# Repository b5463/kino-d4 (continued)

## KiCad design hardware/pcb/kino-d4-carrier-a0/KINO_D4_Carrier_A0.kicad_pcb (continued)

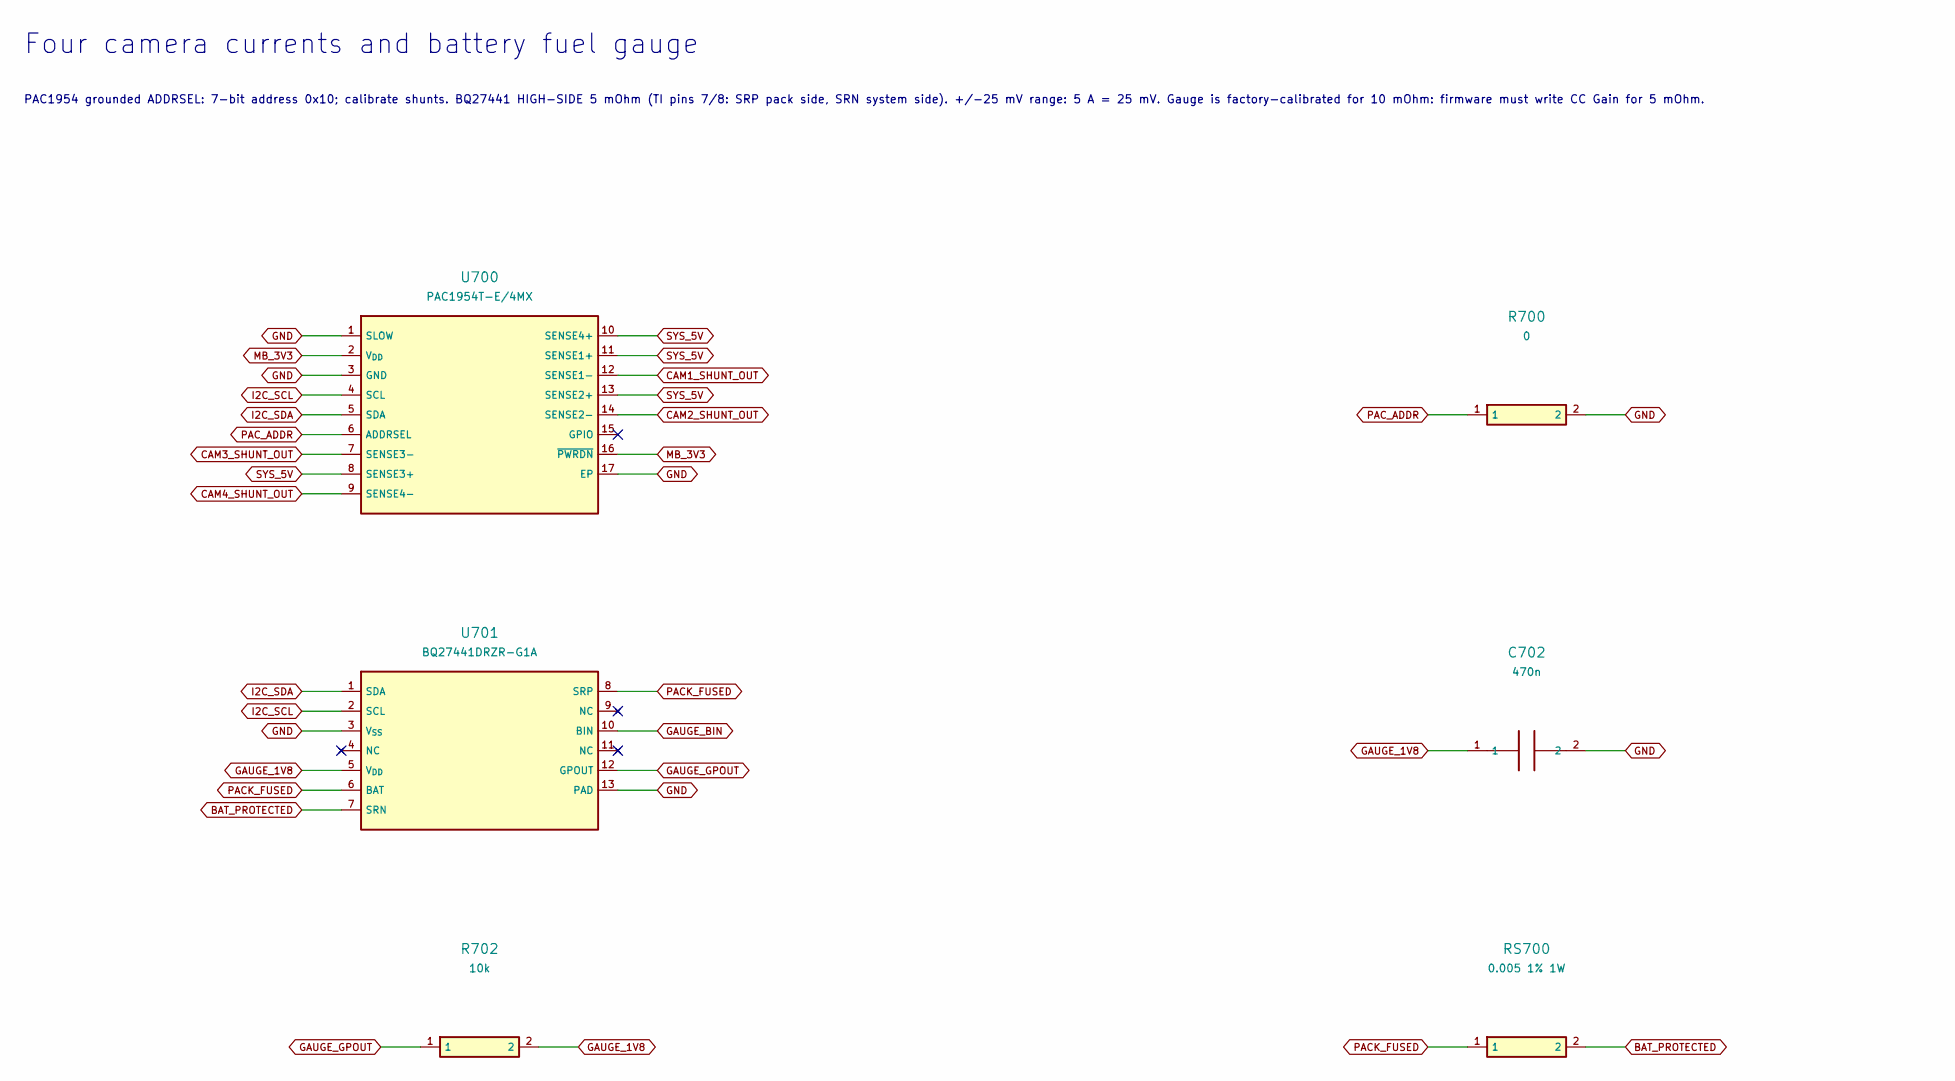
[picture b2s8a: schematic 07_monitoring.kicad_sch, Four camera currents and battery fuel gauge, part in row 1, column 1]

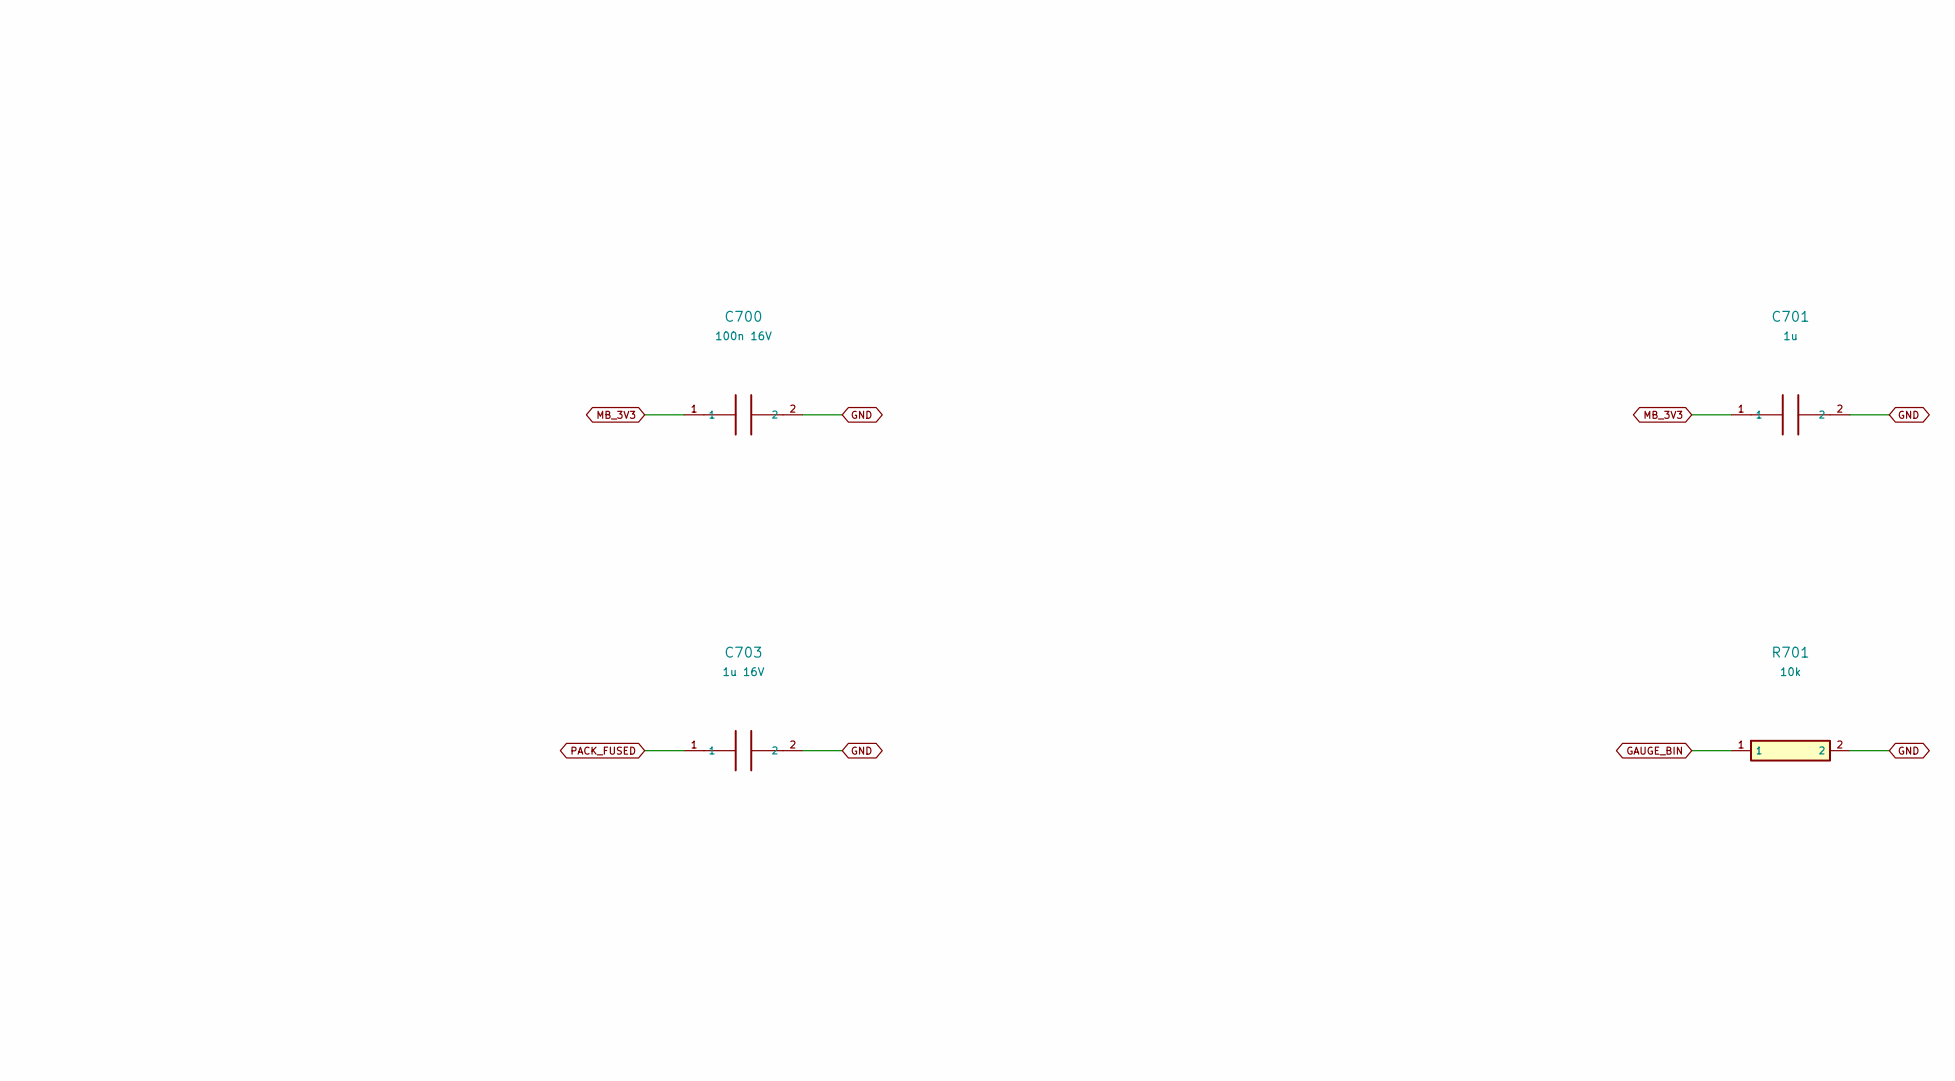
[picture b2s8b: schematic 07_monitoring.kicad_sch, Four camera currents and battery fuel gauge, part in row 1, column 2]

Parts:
C700: 100n 16V; C_0603_1608Metric
C701: 1u; C_0603_1608Metric
C702: 470n; C_0603_1608Metric
C703: 1u 16V; C_0603_1608Metric
R700: 0; R_0603_1608Metric
R701, R702: 10k; R_0603_1608Metric
RS700: 0.005 1% 1W; R_1206_3216Metric
U700: PAC1954T-E/4MX; VQFN-16-1EP_3x3mm_P0.5mm_EP1.1x1.1mm
U701: BQ27441DRZR-G1A; Texas_S-PDSO-N12

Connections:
CAM1_SHUNT_OUT: U700.12 (SENSE1-); also elsewhere on the board
CAM2_SHUNT_OUT: U700.14 (SENSE2-); also elsewhere on the board
CAM3_SHUNT_OUT: U700.7 (SENSE3-); also elsewhere on the board
CAM4_SHUNT_OUT: U700.9 (SENSE4-); also elsewhere on the board
GAUGE_1V8: C702.1, R702.2, U701.5 (V_{DD})
GAUGE_BIN: R701.1, U701.10 (BIN)
I2C_SCL: U700.4 (SCL), U701.2 (SCL); also elsewhere on the board
I2C_SDA: U700.5 (SDA), U701.1 (SDA); also elsewhere on the board
MB_3V3: C700.1, C701.1, U700.2 (V_{DD}), U700.16 (~PWRDN); also elsewhere on the board
unnamed: R702.1, U701.12 (GPOUT)
PAC_ADDR: R700.1, U700.6 (ADDRSEL)
SYS_5V: U700.8 (SENSE3+), U700.10 (SENSE4+), U700.11 (SENSE1+), U700.13 (SENSE2+); also elsewhere on the board

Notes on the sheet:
Four camera currents and battery fuel gauge
PAC1954 grounded ADDRSEL: 7-bit address 0x10; calibrate shunts. BQ27441 HIGH-SIDE 5 mOhm (TI pins 7/8: SRP pack side, SRN system side). +/-25 mV range: 5 A = 25 mV. Gauge is factory-calibrated for 10 mOhm: firmware must write CC Gain for 5 mOhm.

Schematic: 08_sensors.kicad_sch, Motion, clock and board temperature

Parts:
C800, C801, C802, C803: 100n 16V; C_0603_1608Metric
J800: 3V PRIMARY RTC BACKUP; JST_GH_BM02B-GHS-TBT_1x02-1MP_P1.25mm_Vertical
R800: 10k; R_0603_1608Metric
U800: LSM6DSOXTR; LGA-14_3x2.5mm_P0.5mm_LayoutBorder3x4y
U801: RV-3028-C7; MicroCrystal_C7_SON-8_1.5x3.2mm_P0.9mm
U802: TMP117AIDRVR; WSON-6-1EP_2x2mm_P0.65mm_EP1x1.6mm

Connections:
I2C_SCL: U800.13 (SCL), U801.3 (SCL), U802.1 (SCL); also elsewhere on the board
I2C_SDA: U800.14 (SDA), U801.4 (SDA), U802.6 (SDA); also elsewhere on the board
IMU_INT: U800.4 (INT1); also elsewhere on the board
MB_3V3: C800.1, C801.1, C802.1, C803.1, R800.2, U800.5 (VDDIO), U800.8 (VDD), U800.12 (CS), U801.7 (VDD), U802.5 (V+); also elsewhere on the board
RTC_BACKUP: J800.1 (RTC_BACKUP), U801.6 (VBACKUP)
RTC_INT_N: R800.1, U801.2 (~INT); also elsewhere on the board

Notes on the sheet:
Motion, clock and board temperature
IMU mode 1; axes marked on PCB. RTC backup charging must stay disabled for primary cell. No always-on wake promise.

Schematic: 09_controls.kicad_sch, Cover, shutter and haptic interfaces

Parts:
C900, C901: 1u; C_0603_1608Metric
C902: 10u; C_0805_2012Metric
C903: 10n; C_0603_1608Metric
C904: 100n; C_0603_1608Metric
C905: 100n 16V; C_0603_1608Metric
D900, D901, D902: PESD5V0S1BA; D_SOD-323
J900: HAPTIC MOTOR; JST_GH_BM02B-GHS-TBT_1x02-1MP_P1.25mm_Vertical
J901: COVER HALL SENSOR; JST_GH_BM03B-GHS-TBT_1x03-1MP_P1.25mm_Vertical
J902: LOCAL SHUTTER; JST_GH_BM02B-GHS-TBT_1x02-1MP_P1.25mm_Vertical
J903: REMOTE DRY CONTACT; JST_GH_BM02B-GHS-TBT_1x02-1MP_P1.25mm_Vertical
J904: FUNCTION BUTTON; JST_GH_BM02B-GHS-TBT_1x02-1MP_P1.25mm_Vertical
Q900: 2N7002; SOT-23
R900, R905: 100k; R_0603_1608Metric
R901: 1k; R_0603_1608Metric
R902, R903, R906: 10k; R_0603_1608Metric
R904: 47k; R_0603_1608Metric
U900: DRV2605LDGSR; TSSOP-10_3x3mm_P0.5mm
U901: SN74LVC1G14DBVR; SOT-23-5

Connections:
COVER_N: C903.1, R901.2, R902.1; also elsewhere on the board
COVER_RAW: D901.2 (A), J901.3 (COVER_RAW), R901.1
FN_N: J904.1 (FN_N), R906.1; also elsewhere on the board
HAPTIC_EN: R900.1, U900.5 (EN); also elsewhere on the board
HAPTIC_REG: C900.1, U900.1 (REG)
I2C_SCL: U900.2 (SCL); also elsewhere on the board
I2C_SDA: U900.3 (SDA); also elsewhere on the board
MB_3V3: C901.1, C902.1, C905.1, J901.1 (MB_3V3), R902.2, R904.2, R906.2, U900.6 (VDD/NC), U900.10 (VDD), U901.5 (VCC); also elsewhere on the board
MOTOR_N: J900.2 (MOTOR_N), U900.9 (OUT-)
MOTOR_P: J900.1 (MOTOR_P), U900.7 (OUT+)
REMOTE_ACTIVE: Q900.1 (G), R905.1, U901.4 (Y)
REMOTE_CONTACT: D900.2 (A), J903.1 (REMOTE_CONTACT), R903.1
REMOTE_FILTER: C904.1, R903.2, R904.1, U901.2 (A)
SHUTTER_N: D902.2 (A), J902.1 (SHUTTER_N), Q900.3 (D); also elsewhere on the board

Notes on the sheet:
Cover, shutter and haptic interfaces
Passive dry-contact remote only. Haptic firmware must suppress vibration through exposure and settling. Motor MPN remains to be selected.

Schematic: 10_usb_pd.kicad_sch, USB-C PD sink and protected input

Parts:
C1000: 1u 35V; C_0805_2012Metric
C1001, C1002: 1u; C_0603_1608Metric
D1000: BZT52C10; D_SOD-123
D1001: SMF12A; D_SOD-123F
D1002, D1003: PESD24VL1BA; D_SOD-323
J1000: USB4105-GF-A; USB_C_GCT_USB4105_KINO_GND0.05
Q1000, Q1001: AO4407A; SOIC-8_3.9x4.9mm_P1.27mm
R1000, R1003: 100k; R_0603_1608Metric
R1001: 470; R_0603_1608Metric
R1002, R1004: 1k; R_0603_1608Metric
TP1000: USB_VBUS; TestPoint_Pad_D1.5mm
TP1001: PD_9V_OK_N; TestPoint_Pad_D1.5mm
U1000: STUSB4500QTR; QFN-24-1EP_4x4mm_P0.5mm_EP2.7x2.7mm

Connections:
I2C_SCL: U1000.7 (SCL); also elsewhere on the board
I2C_SDA: U1000.8 (SDA); also elsewhere on the board
PD_1V2: C1001.1, U1000.21 (VREG_1V2)
PD_2V7: C1002.1, U1000.23 (VREG_2V7)
PD_9V_OK_N: TP1001.1, U1000.20 (POWER_OK2)
PD_COMMON_SOURCE: D1000.1 (K), Q1000.1 (S), Q1000.2 (S), Q1000.3 (S), Q1001.1 (S), Q1001.2 (S), Q1001.3 (S), R1003.1
PD_DISCH: R1002.2, U1000.9 (DISCH)
PD_GATE: D1000.2 (A), Q1000.4 (G), Q1001.4 (G), R1003.2, R1004.1
PD_RESET: R1000.1, U1000.6 (RESET)
PD_SINK_EN_N: R1004.2, U1000.16 (VBUS_EN_SNK)
PD_VBUS_SENSE: R1001.2, U1000.18 (VBUS_VS_DISCH)
USB_CC1: D1002.1 (K), J1000.A5 (CC1), U1000.1 (CC1DB), U1000.2 (CC1)
USB_CC2: D1003.1 (K), J1000.B5 (CC2), U1000.4 (CC2), U1000.5 (CC2DB)
USB_VBUS: C1000.1, D1001.1 (K), J1000.A4 (VBUS), J1000.A9 (VBUS), J1000.B4 (VBUS), J1000.B9 (VBUS), Q1000.5 (D), Q1000.6 (D), Q1000.7 (D), Q1000.8 (D), R1001.1, TP1000.1, U1000.24 (VDD)

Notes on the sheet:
USB-C PD sink and protected input
Charge-only port. STUSB4500 NVM must be programmed for 5V fallback and 9V/2A. Protection and gate transient review OPEN.

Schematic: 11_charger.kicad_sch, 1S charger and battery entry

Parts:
C1100: 1n 50V; C_0603_1608Metric
C1101: 4.7u 10V; C_0805_2012Metric
C1102, C1103: 47n 16V; C_0603_1608Metric
C1104, C1105, C1107, C1108, C1109, C1111, C1112, C1113, C1114, C1115, C1117, C1118: 10u 35V X7R; C_1206_3216Metric
C1106, C1110, C1116, C1119: 100n 35V; C_0603_1608Metric
F1100: 7A fast 1206; Fuse_1206_3216Metric
J1100: PROTECTED 1S PACK / NTC; JST_VH_B3P-VH_1x03_P3.96mm_Vertical
L1100: 1.0uH 14.1A Isat; L_TDK_SPM6530
R1100: 3.00k 1%; R_0603_1608Metric
R1101: 100; R_0603_1608Metric
R1102: 100k; R_0603_1608Metric
R1104, R1107: 30.1k 1%; R_0603_1608Metric
R1105: 10k 1%; R_0603_1608Metric
R1106: 5.23k 1%; R_0603_1608Metric
R1108: 0; R_0603_1608Metric
R1109: 10k; R_0603_1608Metric
R1110: 10k; R_0603_1608Metric; not fitted
TP1100: CHARGE_STAT_N; TestPoint_Pad_D1.5mm
TP1101: SYS_RAW; TestPoint_Pad_D1.5mm
U1100: BQ25798RQMR; Texas_RQM0029A_VQFN-29_4x4mm_P0.4mm

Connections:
CHARGE_CE_N: R1102.1, R1110.1, U1100.13 (~CE); also elsewhere on the board
CHARGE_STAT_N: R1109.1, TP1100.1, U1100.1 (STAT); also elsewhere on the board
CHG_BATP: R1101.2, U1100.18 (BATP)
CHG_BTST1: C1102.1, U1100.4 (BTST1)
CHG_BTST2: C1103.1, U1100.19 (BTST2)
CHG_ILIM: R1104.2, R1105.1, U1100.17 (ILIM_HIZ)
CHG_PMID: C1107.1, C1108.1, C1109.1, C1110.1, U1100.29 (PMID)
CHG_PROG: R1100.1, U1100.20 (PROG)
CHG_SDRV: C1100.1, U1100.24 (SDRV)
CHG_SW1: C1102.2, L1100.1, U1100.28 (SW1)
CHG_SW2: C1103.2, L1100.2, U1100.26 (SW2)
CHG_TS: R1106.2, R1107.1, R1108.1, U1100.16 (TS)
I2C_SCL: U1100.14 (SCL); also elsewhere on the board
I2C_SDA: U1100.15 (SDA); also elsewhere on the board
MB_3V3: R1109.2; also elsewhere on the board
PACK_NTC: J1100.2 (PACK_NTC), R1108.2
PACK_PLUS: F1100.1, J1100.1 (PACK_PLUS)
SYS_RAW: C1111.1, C1112.1, C1113.1, C1114.1, C1115.1, C1116.1, TP1101.1, U1100.25 (SYS); also elsewhere on the board

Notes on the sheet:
1S charger and battery entry
CE pulled LOW: charges with the camera off, POR defaults 4.2 V / 1 A (PROG 3.00k, TI tables 7-1/7-2). 103AT-2 pack NTC, TS window 1-60 C (TI RT1 5.24k / RT2 30.31k). Open or shorted NTC suspends charge. Fit R1110 only to inhibit charging at bring-up.

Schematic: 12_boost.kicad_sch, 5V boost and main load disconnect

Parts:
C1200: 3.3n 50V; C_0603_1608Metric
C1201: 100p; C_0603_1608Metric; not fitted
C1202: 4.7u 16V; C_0603_1608Metric
C1203: 100n; C_0603_1608Metric
C1204, C1206, C1207, C1208, C1209, C1210, C1211: 22u 10V; C_1206_3216Metric
C1205: 100n 16V; C_0603_1608Metric
C1212: 10u; C_0805_2012Metric
C1213: 22u; C_0805_2012Metric
D1200: SS34; D_SMA
JP1200: REMOVE FOR P4 USB SERVICE; PinHeader_1x02_P2.54mm_Vertical
L1200: 2.2uH 19.6A Isat; L_Coilcraft_XAL7070-XXX
L1201: 2.2uH 1.5A; L_Taiyo-Yuden_NR-30xx
Q1200, Q1201: AO4407A; SOIC-8_3.9x4.9mm_P1.27mm
Q1202: 2N7002; SOT-23
R1200: 110k 0.1%; R_0603_1608Metric
R1201: 15k 0.1%; R_0603_1608Metric
R1202: 20.5k 1%; R_0603_1608Metric
R1203: 100k; R_0603_1608Metric
TP1200: SYS_5V; TestPoint_Pad_D1.5mm
TP1201: MB_3V3; TestPoint_Pad_D1.5mm
TP1202: GND; TestPoint_Pad_D1.5mm
U1200: TPS61288LRQQR; TPS61288_RQQ0011A_DRAFT
U1201: TPS62162DSGR; Texas_DSG0008A_WSON-8-1EP_2x2mm_P0.5mm_EP0.9x1.6mm_ThermalV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

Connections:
BOOST_5V: C1206.1, C1207.1, C1208.1, C1209.1, C1210.1, C1211.1, Q1200.5 (D), Q1200.6 (D), Q1200.7 (D), Q1200.8 (D), R1200.1, U1200.5 (VOUT)
BOOST_BST: C1203.1, U1200.8 (BST)
BOOST_COMP: C1201.1, R1202.1, U1200.2 (COMP)
BOOST_COMP_RC: C1200.1, R1202.2
BOOST_ENABLE: Q1202.1 (G), U1200.6 (EN); also elsewhere on the board
BOOST_FB: R1200.2, R1201.1, U1200.1 (FB)
BOOST_SW: C1203.2, L1200.2, U1200.4 (SW), U1200.9 (SW)
BOOST_VCC: C1202.1, U1200.11 (VCC)
BUCK_SW: L1201.1, U1201.7 (SW)
MAIN_COMMON: Q1200.1 (S), Q1200.2 (S), Q1200.3 (S), Q1201.1 (S), Q1201.2 (S), Q1201.3 (S), R1203.1
MAIN_GATE: Q1200.4 (G), Q1201.4 (G), Q1202.3 (D), R1203.2
MB_3V3: C1213.1, L1201.2, TP1201.1, U1201.6 (VOS); also elsewhere on the board
P4_5V: JP1200.2 (P4_5V); also elsewhere on the board
P4_5V_ISO: D1200.1 (K), JP1200.1 (P4_5V_ISO)
SYS_5V: C1212.1, D1200.2 (A), Q1201.5 (D), Q1201.6 (D), Q1201.7 (D), Q1201.8 (D), TP1200.1, U1201.2 (VIN), U1201.3 (EN); also elsewhere on the board
SYS_RAW: C1204.1, C1205.1, L1200.1, U1200.7 (VIN); also elsewhere on the board

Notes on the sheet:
5V boost and main load disconnect
5V = 0.6*(1+110k/15k). L Isat 19.6 A > ILIM 17.1 A max (TI 9.2.2.2). Comp per TI eq 12-14: fc 8-16 kHz, PM > 68 deg over Co 50-110 uF, L +/-20 %, Vin 3.0-4.3 V. Calculated; measure loop on bench.

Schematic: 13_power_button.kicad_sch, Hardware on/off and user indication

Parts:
C1300: 100n 16V; C_0603_1608Metric
C1301: 1.5u 16V; C_0603_1608Metric
D1300: LED GREEN; LED_0603_1608Metric
D1301: LED AMBER; LED_0603_1608Metric
J1300: POWER PUSHBUTTON; JST_GH_BM02B-GHS-TBT_1x02-1MP_P1.25mm_Vertical
Q1300: 2N7002; SOT-23
R1300, R1301: 100k; R_0603_1608Metric
R1302: 10k; R_0603_1608Metric
R1303, R1304: 2.2k; R_0603_1608Metric
U1300: LTC2955ITS8-1; TSOT-23-8

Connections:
BOOST_ENABLE: U1300.7 (EN); also elsewhere on the board
CHARGE_LED_A: D1301.2 (A), R1304.2
CHARGE_STAT_N: D1301.1 (K); also elsewhere on the board
MB_3V3: R1302.2, R1303.1, R1304.1; also elsewhere on the board
POWER_INT_N: R1302.1, U1300.8 (INT_N); also elsewhere on the board
POWER_KILL_N: Q1300.3 (D), R1300.1, U1300.2 (KILL)
POWER_LED_A: D1300.2 (A), R1303.2
POWER_PB_N: J1300.1 (POWER_PB_N), U1300.5 (PB_N)
POWER_TMR: C1301.1, U1300.3 (TMR)
SOFT_KILL: Q1300.1 (G), R1301.1; also elsewhere on the board
SYS_RAW: C1300.1, R1300.2, U1300.6 (VIN); also elsewhere on the board

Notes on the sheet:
Hardware on/off and user indication
Power controller TS8 pin map checked against manufacturer package drawing; EN is pin 7. KILL is pulled high until software requests shutdown. Long-hold target remains provisional.

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
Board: 4 copper layers, 247 parts (0 on the bottom side), 188 nets, no tracks yet.

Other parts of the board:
H1, H2, H3, H4: P4 M2 insert mount; MountingHole_2.2mm_M2
Q1100: 2N7002; SOT-23
R1103: 100k; R_0603_1608Metric

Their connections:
CHARGE_ARM: Q1100.1, R1103.1; also elsewhere on the board
CHARGE_CE_N: Q1100.3; also elsewhere on the board

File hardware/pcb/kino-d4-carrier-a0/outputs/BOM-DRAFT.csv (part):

Reference,Value,MPN_candidate,Footprint,DNP,Status,Design_note,Source
J100,P4 JP1 - 26 pin IDC,Wurth Elektronik 61202621621,Connector_IDC:IDC-Header_2x13_P2.54mm_Vertical,False,ENGINEERING_DRAFT,1:1 electrical pin numbering; verify cable and mating views.,https://www.we-online.com/components/products/datasheet/6120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
J101,C6 service - 3V3 sense only,Wurth Elektronik 61300611121,Connector_PinHeader_2.54mm:PinHeader_1x06_P2.54mm_Vertical,False,ENGINEERING_DRAFT,,https://www.we-online.com/components/products/datasheet/6130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
U100,TCA9517ADGKR,TCA9517ADGKR,Package_SO:VSSOP-8_3x3mm_P0.65mm,False,ENGINEERING_DRAFT,B side is local. Do not cascade another B-side offset buffer on local bus.,https://www.ti.com/lit/ds/symlink/tca9517a.pdf
R100,10k,RC0603FR-0710KL,Resistor_SMD:R_0603_1608Metric,False,ENGINEERING_DRAFT,,https://www.yageogroup.com/component-documentation/download/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
R101,1M,RC0603FR-071ML,Resistor_SMD:R_0603_1608Metric,False,ENGINEERING_DRAFT,,https://www.yageogroup.com/component-documentation/download/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
R102,4.7k,RC0603FR-074K7L,Resistor_SMD:R_0603_1608Metric,False,ENGINEERING_DRAFT,,https://www.yageogroup.com/component-documentation/download/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
R103,4.7k,RC0603FR-074K7L,Resistor_SMD:R_0603_1608Metric,False,ENGINEERING_DRAFT,,https://www.yageogroup.com/component-documentation/download/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
C100,100n 16V,YAGEO CC0603KRX7R9BB104,Capacitor_SMD:C_0603_1608Metric,False,ENGINEERING_DRAFT,,https://www.yageogroup.com/component-documentation/download/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
R104,100k,RC0603FR-07100KL,Resistor_SMD:R_0603_1608Metric,False,ENGINEERING_DRAFT,,https://www.yageogroup.com/component-documentation/download/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
J102,3V3 I2C accessory,JST BM04B-GHS-TBT(LF)(SN),Connector_JST:JST_GH_BM04B-GHS-TBT_1x04-1MP_P1.25mm_Vertical,False,ENGINEERING_DRAFT,,https://www.jst-mfg.com/product/pdf/eng/eGH.pdf
F100,PTC 100mA - select,Bel Fuse 0ZCJ0010FF2E,Fuse:Fuse_1206_3216Metric,False,ENGINEERING_DRAFT,Accessory protection and ESD review open.,https://www.belfuse.com/media/datasheets/products/circuit-pr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
TP100,P4_3V3_TEST,P4_3V3_TEST,TestPoint:TestPoint_Pad_D1.5mm,False,ENGINEERING_DRAFT,,
TP101,SYNC_MASTER,SYNC_MASTER,TestPoint:TestPoint_Pad_D1.5mm,False,ENGINEERING_DRAFT,,
TP102,P4_5V,P4_5V,TestPoint:TestPoint_Pad_D1.5mm,False,ENGINEERING_DRAFT,,
J200,XIAO ESP32-S3 Sense socket,Wurth Elektronik 61300711821,KINO_A0:XIAO_Socket_15.24mm,False,ENGINEERING_DRAFT,Two 1x07 sockets; 22 mm camera pitch. 5V shared with node USB; isolate via jumper for USB service.,https://www.we-online.com/components/products/datasheet/6130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
J201,GPIO breakout - SD/strap restrictions,Wurth Elektronik 61301021121,Connector_PinHeader_2.54mm:PinHeader_2x05_P2.54mm_Vertical,False,ENGINEERING_DRAFT,,https://www.we-online.com/components/products/datasheet/6130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
JP200,REMOVE FOR NODE USB,Wurth Elektronik 61300211121 + shunt 60900213421,Connector_PinHeader_2.54mm:PinHeader_1x02_P2.54mm_Vertical,False,ENGINEERING_DRAFT,"Fit removable shunt during camera operation, remove before USB cable insertion.",https://www.we-online.com/components/products/datasheet/6130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 ; https://www.we-online.com/components/products/datasheet/6090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
U200,TXU0304PWR,TXU0304PWR,Package_SO:TSSOP-14_4.4x5mm_P0.65mm,False,ENGINEERING_DRAFT,,https://www.ti.com/lit/ds/symlink/txu0304.pdf
R200,33,RC0603FR-0733RL,Resistor_SMD:R_0603_1608Metric,False,ENGINEERING_DRAFT,,https://www.yageogroup.com/component-documentation/download/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
R201,33,RC0603FR-0733RL,Resistor_SMD:R_0603_1608Metric,False,ENGINEERING_DRAFT,,https://www.yageogroup.com/component-documentation/download/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
R202,33,RC0603FR-0733RL,Resistor_SMD:R_0603_1608Metric,False,ENGINEERING_DRAFT,,https://www.yageogroup.com/component-documentation/download/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
C200,100n 16V,YAGEO CC0603KRX7R9BB104,Capacitor_SMD:C_0603_1608Metric,False,ENGINEERING_DRAFT,,https://www.yageogroup.com/component-documentation/download/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
C201,100n 16V,YAGEO CC0603KRX7R9BB104,Capacitor_SMD:C_0603_1608Metric,False,ENGINEERING_DRAFT,,https://www.yageogroup.com/component-documentation/download/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
U201,TPS2553DBVR,TPS2553DBVR,Package_TO_SOT_SMD:SOT-23-6,False,ENGINEERING_DRAFT,,https://www.ti.com/lit/ds/symlink/tps2553.pdf
R203,25.5k 1%,RC0603FR-0725K5L,Resistor_SMD:R_0603_1608Metric,False,ENGINEERING_DRAFT,Approx. 1A target; verify min/max and startup before release.,https://www.yageogroup.com/component-documentation/download/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
R204,10k,RC0603FR-0710KL,Resistor_SMD:R_0603_1608Metric,False,ENGINEERING_DRAFT,,https://www.yageogroup.com/component-documentation/download/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
R205,100k,RC0603FR-07100KL,Resistor_SMD:R_0603_1608Metric,False,ENGINEERING_DRAFT,,https://www.yageogroup.com/component-documentation/download/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
RS200,0.020 1% 0.5W,Vishay Dale WSLP1206R0200FEA,Resistor_SMD:R_1206_3216Metric,False,ENGINEERING_DRAFT,Kelvin sense required; exact current-sense resistor MPN pending.,https://www.vishay.com/docs/30122/wslp.pdf
D200,SS34,Diodes Incorporated B340A-13-F,Diode_SMD:D_SMA,False,ENGINEERING_DRAFT,Reverse node USB-to-carrier isolation; does not prevent carrier-to-host VBUS feed without removing jumper.,https://www.diodes.com/datasheet/download/B340A.pdf
C202,1u 16V,Samsung Electro-Mechanics CL10A105KB8NNNC,Capacitor_SMD:C_0603_1608Metric,False,ENGINEERING_DRAFT,,https://weblib.samsungsem.com/mlcc/mlcc-ec-data-sheet.do?par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
C203,22u 10V,Samsung Electro-Mechanics CL21A226MAQNNNE,Capacitor_SMD:C_0805_2012Metric,False,ENGINEERING_DRAFT,,https://weblib.samsungsem.com/mlcc/mlcc-ec-data-sheet.do?par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
C204,100n 16V,YAGEO CC0603KRX7R9BB104,Capacitor_SMD:C_0603_1608Metric,False,ENGINEERING_DRAFT,,https://www.yageogroup.com/component-documentation/download/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
TP200,CAM1_5V,CAM1_5V,TestPoint:TestPoint_Pad_D1.5mm,False,ENGINEERING_DRAFT,,
TP201,CAM1_SYNC,CAM1_SYNC,TestPoint:TestPoint_Pad_D1.5mm,False,ENGINEERING_DRAFT,,
J300,XIAO ESP32-S3 Sense socket,Wurth Elektronik 61300711821,KINO_A0:XIAO_Socket_15.24mm,False,ENGINEERING_DRAFT,Two 1x07 sockets; 22 mm camera pitch. 5V shared with node USB; isolate via jumper for USB service.,https://www.we-online.com/components/products/datasheet/6130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
J301,GPIO breakout - SD/strap restrictions,Wurth Elektronik 61301021121,Connector_PinHeader_2.54mm:PinHeader_2x05_P2.54mm_Vertical,False,ENGINEERING_DRAFT,,https://www.we-online.com/components/products/datasheet/6130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
JP300,REMOVE FOR NODE USB,Wurth Elektronik 61300211121 + shunt 60900213421,Connector_PinHeader_2.54mm:PinHeader_1x02_P2.54mm_Vertical,False,ENGINEERING_DRAFT,"Fit removable shunt during camera operation, remove before USB cable insertion.",https://www.we-online.com/components/products/datasheet/6130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 ; https://www.we-online.com/components/products/datasheet/6090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
U300,TXU0304PWR,TXU0304PWR,Package_SO:TSSOP-14_4.4x5mm_P0.65mm,False,ENGINEERING_DRAFT,,https://www.ti.com/lit/ds/symlink/txu0304.pdf
R300,33,RC0603FR-0733RL,Resistor_SMD:R_0603_1608Metric,False,ENGINEERING_DRAFT,,https://www.yageogroup.com/component-documentation/download/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
R301,33,RC0603FR-0733RL,Resistor_SMD:R_0603_1608Metric,False,ENGINEERING_DRAFT,,https://www.yageogroup.com/component-documentation/download/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
R302,33,RC0603FR-0733RL,Resistor_SMD:R_0603_1608Metric,False,ENGINEERING_DRAFT,,https://www.yageogroup.com/component-documentation/download/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
C300,100n 16V,YAGEO CC0603KRX7R9BB104,Capacitor_SMD:C_0603_1608Metric,False,ENGINEERING_DRAFT,,https://www.yageogroup.com/component-documentation/download/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
C301,100n 16V,YAGEO CC0603KRX7R9BB104,Capacitor_SMD:C_0603_1608Metric,False,ENGINEERING_DRAFT,,https://www.yageogroup.com/component-documentation/download/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
U301,TPS2553DBVR,TPS2553DBVR,Package_TO_SOT_SMD:SOT-23-6,False,ENGINEERING_DRAFT,,https://www.ti.com/lit/ds/symlink/tps2553.pdf
R303,25.5k 1%,RC0603FR-0725K5L,Resistor_SMD:R_0603_1608Metric,False,ENGINEERING_DRAFT,Approx. 1A target; verify min/max and startup before release.,https://www.yageogroup.com/component-documentation/download/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
R304,10k,RC0603FR-0710KL,Resistor_SMD:R_0603_1608Metric,False,ENGINEERING_DRAFT,,https://www.yageogroup.com/component-documentation/download/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
